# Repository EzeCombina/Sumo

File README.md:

2022: Primera versión del robot ---> ¿?

2023: Segunda versión del robot ---> MEGAPODA - Hecho con SolidWorks 2020 -

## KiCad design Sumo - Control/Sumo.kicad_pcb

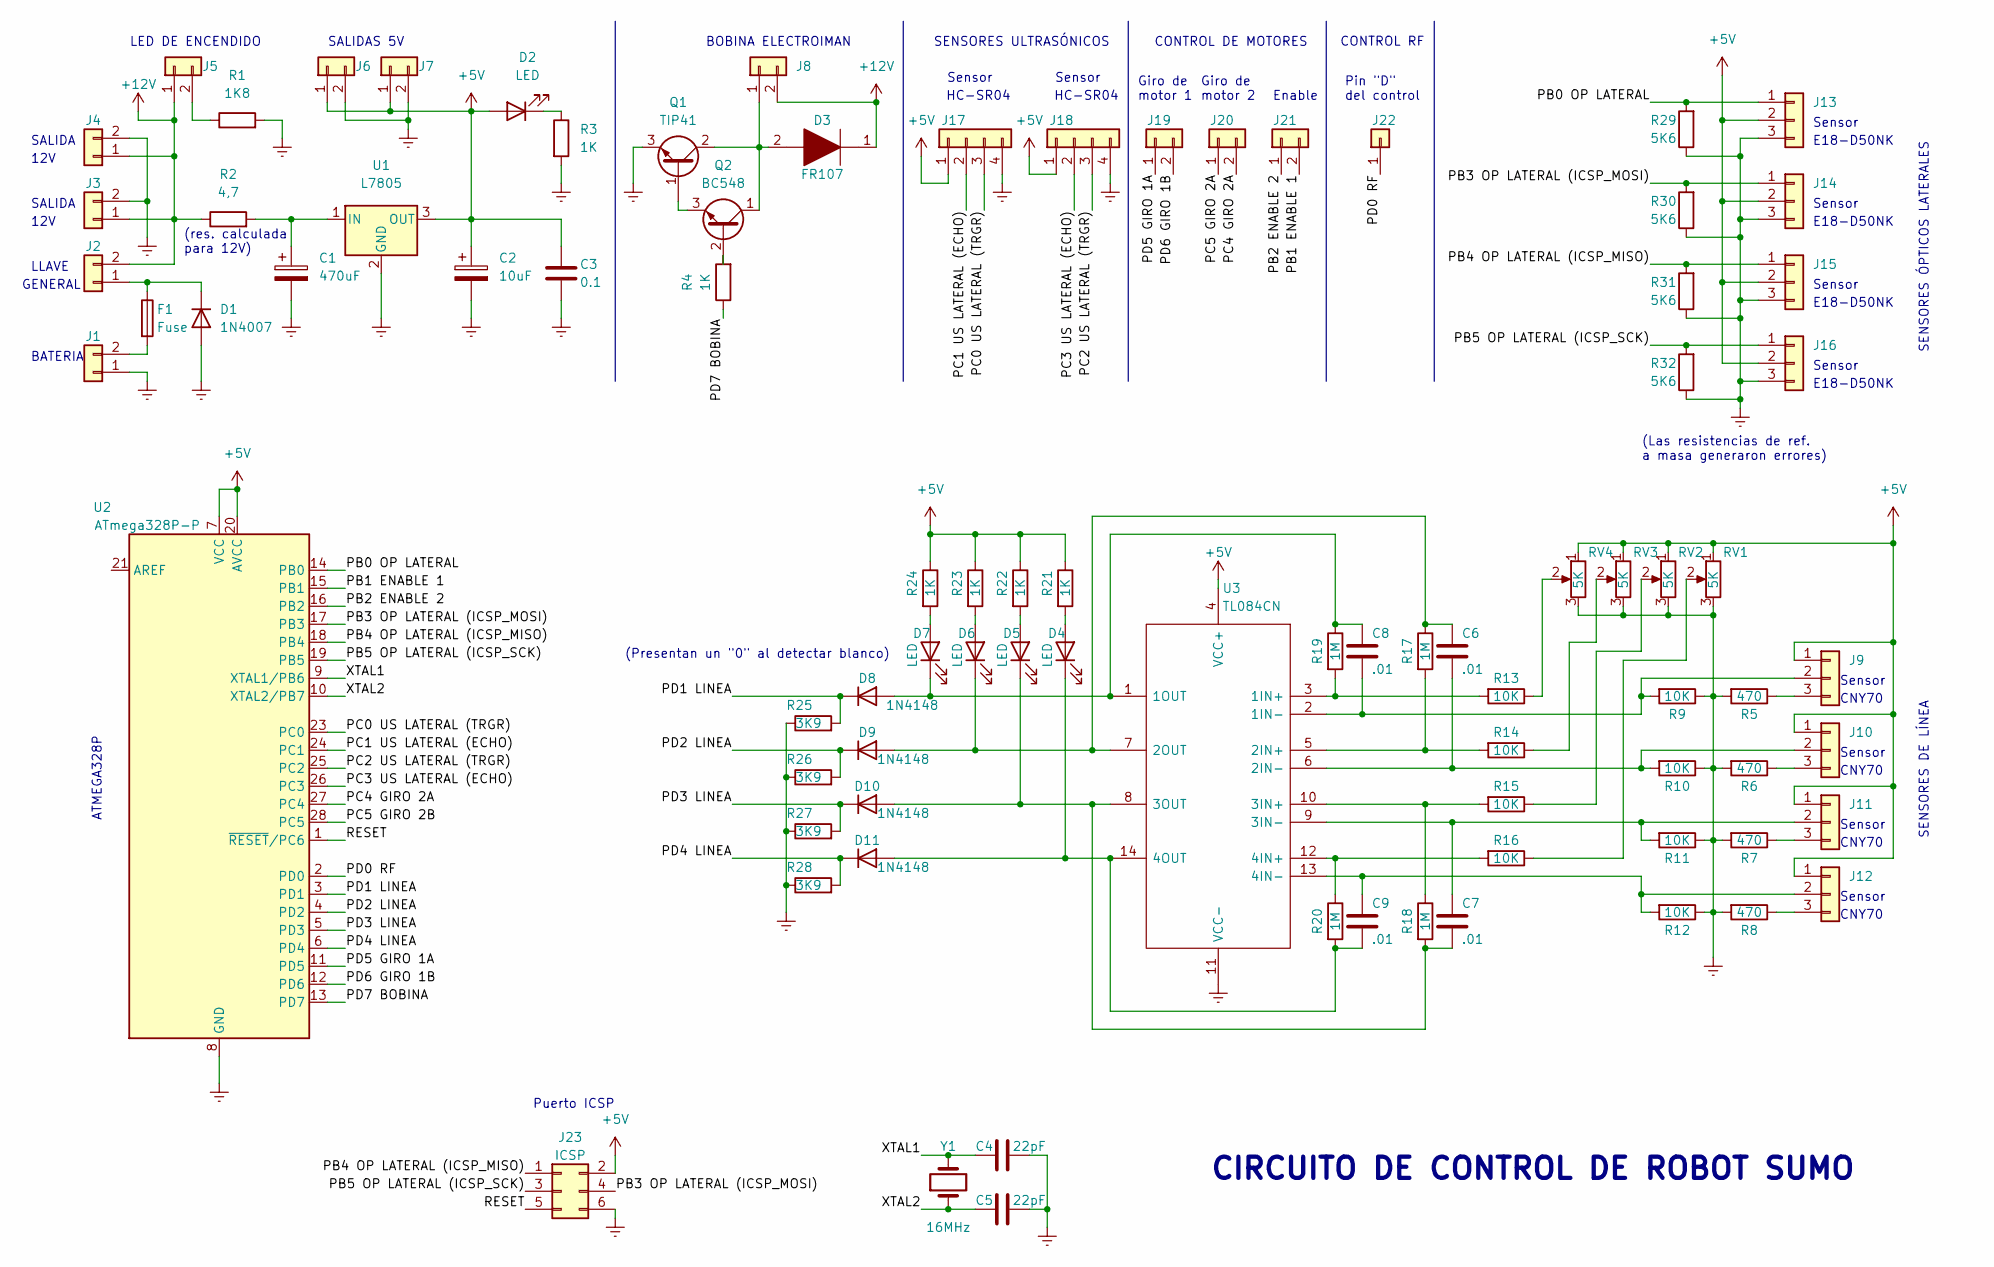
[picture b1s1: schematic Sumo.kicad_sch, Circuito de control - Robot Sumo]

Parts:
C1: 470uF; CP_Radial_D10.0mm_P5.00mm
C2: 10uF; CP_Radial_D5.0mm_P2.00mm
C3: 0.1; C_Disc_D4.3mm_W1.9mm_P5.00mm
C4, C5: 22pF; C_Disc_D4.3mm_W1.9mm_P5.00mm
C6, C7, C8, C9: .01; C_Disc_D4.3mm_W1.9mm_P5.00mm
D1: 1N4007; D_DO-41_SOD81_P10.16mm_Horizontal
D2, D4, D5, D6, D7: LED; LED_D3.0mm
D3: FR107; DIOAD1070W78L470D235P; Manufacturer_Part_Number FR107; Mouser Part Number N/A
D8, D9, D10, D11: 1N4148; D_DO-35_SOD27_P7.62mm_Horizontal
F1: Fuse; JST_PH_B2B-PH-K_1x02_P2.00mm_Vertical
J1, J2, J3, J4, J5, J6, J7, J8, J19, J20: Conn_01x02; JST_PH_B2B-PH-K_1x02_P2.00mm_Vertical
J9: J; JST_PH_B4B-PH-K_1x04_P2.00mm_Vertical
J10, J11, J12, J13, J14, J15, J16: Conn_01x03; JST_PH_B4B-PH-K_1x04_P2.00mm_Vertical
J17, J18: Conn_01x04; JST_PH_B4B-PH-K_1x04_P2.00mm_Vertical
J21: Conn_01x02; JST_EH_B2B-EH-A_1x02_P2.50mm_Vertical
J22: Conn_01x01; JST_EH_B2B-EH-A_1x02_P2.50mm_Vertical
J23: ICSP; PinHeader_2x03_P2.54mm_Vertical
Q1: TIP41; TO-220-3_Vertical
Q2: BC548; TO-92_Inline_Wide
R1: 1K8; R_Axial_DIN0204_L3.6mm_D1.6mm_P7.62mm_Horizontal
R2: 4,7; R_Axial_DIN0204_L3.6mm_D1.6mm_P7.62mm_Horizontal
R3, R4, R21, R22, R23, R24: 1K; R_Axial_DIN0204_L3.6mm_D1.6mm_P7.62mm_Horizontal
R5, R6, R7, R8: 470; R_Axial_DIN0204_L3.6mm_D1.6mm_P5.08mm_Horizontal
R9, R10, R11, R12, R13, R14, R15, R16: 10K; R_Axial_DIN0204_L3.6mm_D1.6mm_P5.08mm_Horizontal
R17, R18, R19, R20: 1M; R_Axial_DIN0204_L3.6mm_D1.6mm_P5.08mm_Horizontal
R25, R26, R27, R28: 3K9; R_Axial_DIN0204_L3.6mm_D1.6mm_P5.08mm_Horizontal
R29, R30, R31, R32: 5K6; R_Axial_DIN0204_L3.6mm_D1.6mm_P5.08mm_Horizontal
RV1, RV2, RV3, RV4: 5K; Potentiometer_Bourns_3296W_Vertical
U1: L7805; TO-220-3_Vertical
U2: ATmega328P-P; DIP-28_W7.62mm
U3: TL084CN; DIP794W53P254L1930H508Q14N; Manufacturer_Part_Number TL084CN; Mouser Part Number 595-TL084CN
Y1: 16MHz; Crystal_HC49-U_Vertical

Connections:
+5V: C2.1, C3.1, D2.2 (A), J6.1, J7.1, J9.1, J10.1, J11.1, J12.1, J13.2, J14.2, J15.2, J16.2, J17.1, J18.1, J23.2, R21.1, R22.1, R23.1, R24.1, RV1.1, RV2.1, RV3.1, RV4.1, U1.3 (OUT), U2.7 (VCC), U2.20 (AVCC), U3.4 (VCC+)
+12V: D3.1, J2.2, J3.1, J4.1, J5.1, J8.2, R2.1
/PB0 OP LATERAL: J13.1, R29.2, U2.14 (PB0)
/PB1 GIRO 2A: J21.2, U2.15 (PB1)
/PB2 GIRO 2B: J21.1, U2.16 (PB2)
/PB3 OP LATERAL (ICSP_MOSI): J14.1, J23.4, R30.2, U2.17 (PB3)
/PB4 OP LATERAL (ICSP_MISO): J15.1, J23.1, R31.2, U2.18 (PB4)
/PB5 OP LATERAL (ICSP_SCK): J16.1, J23.3, R32.2, U2.19 (PB5)
/PC0 US LATERAL (TRGR): J17.3, U2.23 (PC0)
/PC1 US LATERAL (ECHO): J17.2, U2.24 (PC1)
/PC2 US LATERAL (TRGR): J18.3, U2.25 (PC2)
/PC3 US LATERAL (ECHO): J18.2, U2.26 (PC3)
/PD0: J22.1, U2.2 (PD0)
/PD1 LINEA: D8.1 (K), R25.2, U2.3 (PD1)
/PD2 LINEA: D9.1 (K), R26.2, U2.4 (PD2)
/PD3 LINEA: D10.1 (K), R27.2, U2.5 (PD3)
/PD4 LINEA: D11.1 (K), R28.2, U2.6 (PD4)
/PD5 GIRO 1A: J19.1, U2.11 (PD5)
/PD6 GIRO 1B: J19.2, U2.12 (PD6)
/PD7 BOBINA: R4.1, U2.13 (PD7)
/RESET: J23.5, U2.1 (~RESET/PC6)
/XTAL1: C4.2, U2.9 (XTAL1/PB6), Y1.2
/XTAL2: C5.1, U2.10 (XTAL2/PB7), Y1.1
Earth: C1.2, C2.2, C3.2, C4.1, C5.2, D1.2 (A), J1.1, J3.2, J4.2, J6.2, J7.2, J13.3, J13.4, J14.3, J15.3, J16.3, J17.4, J18.4, J23.6, Q1.3 (E), R1.2, R3.2, R5.2, R6.2, R7.2, R8.2, R9.1, R10.1, R11.1, R12.1, R25.1, R26.1, R27.1, R28.1, R29.1, R30.1, R31.1, R32.1, RV1.3, RV2.3, RV3.3, RV4.3, U1.2 (GND), U2.8 (GND), U2.22 (GND), U3.11 (VCC-)
unnamed: C1.1, R2.2, U1.1 (IN)
unnamed: C6.1, J10.2, R10.2, U3.6 (2IN-)
unnamed: C6.2, D6.1 (K), D9.2 (A), R17.1, U3.7 (2OUT)
unnamed: C7.1, D5.1 (K), D10.2 (A), R18.2, U3.8 (3OUT)
unnamed: C7.2, J11.2, R11.2, U3.9 (3IN-)
unnamed: C8.1, J9.2, R9.2, U3.2 (1IN-)
unnamed: C8.2, D7.1 (K), D8.2 (A), R19.1, U3.1 (1OUT)
unnamed: C9.1, D4.1 (K), D11.2 (A), R20.2, U3.14 (4OUT)
unnamed: C9.2, J12.2, R12.2, U3.13 (4IN-)
unnamed: D1.1 (K), F1.1, J2.1
unnamed: D2.1 (K), R3.1
unnamed: D3.2, J8.1, Q1.2 (C), Q2.1 (C)
unnamed: D4.2 (A), R21.2
unnamed: D5.2 (A), R22.2
unnamed: D6.2 (A), R23.2
unnamed: D7.2 (A), R24.2
unnamed: F1.2, J1.2
unnamed: J5.2, R1.1
unnamed: J9.3, R5.1
unnamed: J10.3, R6.1
unnamed: J11.3, R7.1
unnamed: J12.3, R8.1
unnamed: Q1.1 (B), Q2.3 (E)
unnamed: Q2.2 (B), R4.2
unnamed: R13.1, RV4.2
unnamed: R13.2, R19.2, U3.3 (1IN+)
unnamed: R14.1, RV3.2
unnamed: R14.2, R17.2, U3.5 (2IN+)
unnamed: R15.1, RV2.2
unnamed: R15.2, R18.1, U3.10 (3IN+)
unnamed: R16.1, RV1.2
unnamed: R16.2, R20.1, U3.12 (4IN+)

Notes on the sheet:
SENSORES DE LÍNEA
SENSORES ÓPTICOS LATERALES
E18-D50NK
LED DE ENCENDIDO
Puerto ICSP
(Presentan un "0" al detectar blanco)
CNY70
12V
Sensor
SENSORES ULTRASÓNICOS
Enable
Giro de motor 1
Pin "D" del control
Giro de motor 2
SALIDA
GENERAL
BOBINA ELECTROIMAN
LLAVE
BATERIA
CONTROL RF
(res. calculada para 12V)
ATMEGA328P
CONTROL DE MOTORES
CIRCUITO DE CONTROL DE ROBOT SUMO
HC-SR04
(Las resistencias de ref. a masa generaron errores)
SALIDAS 5V

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
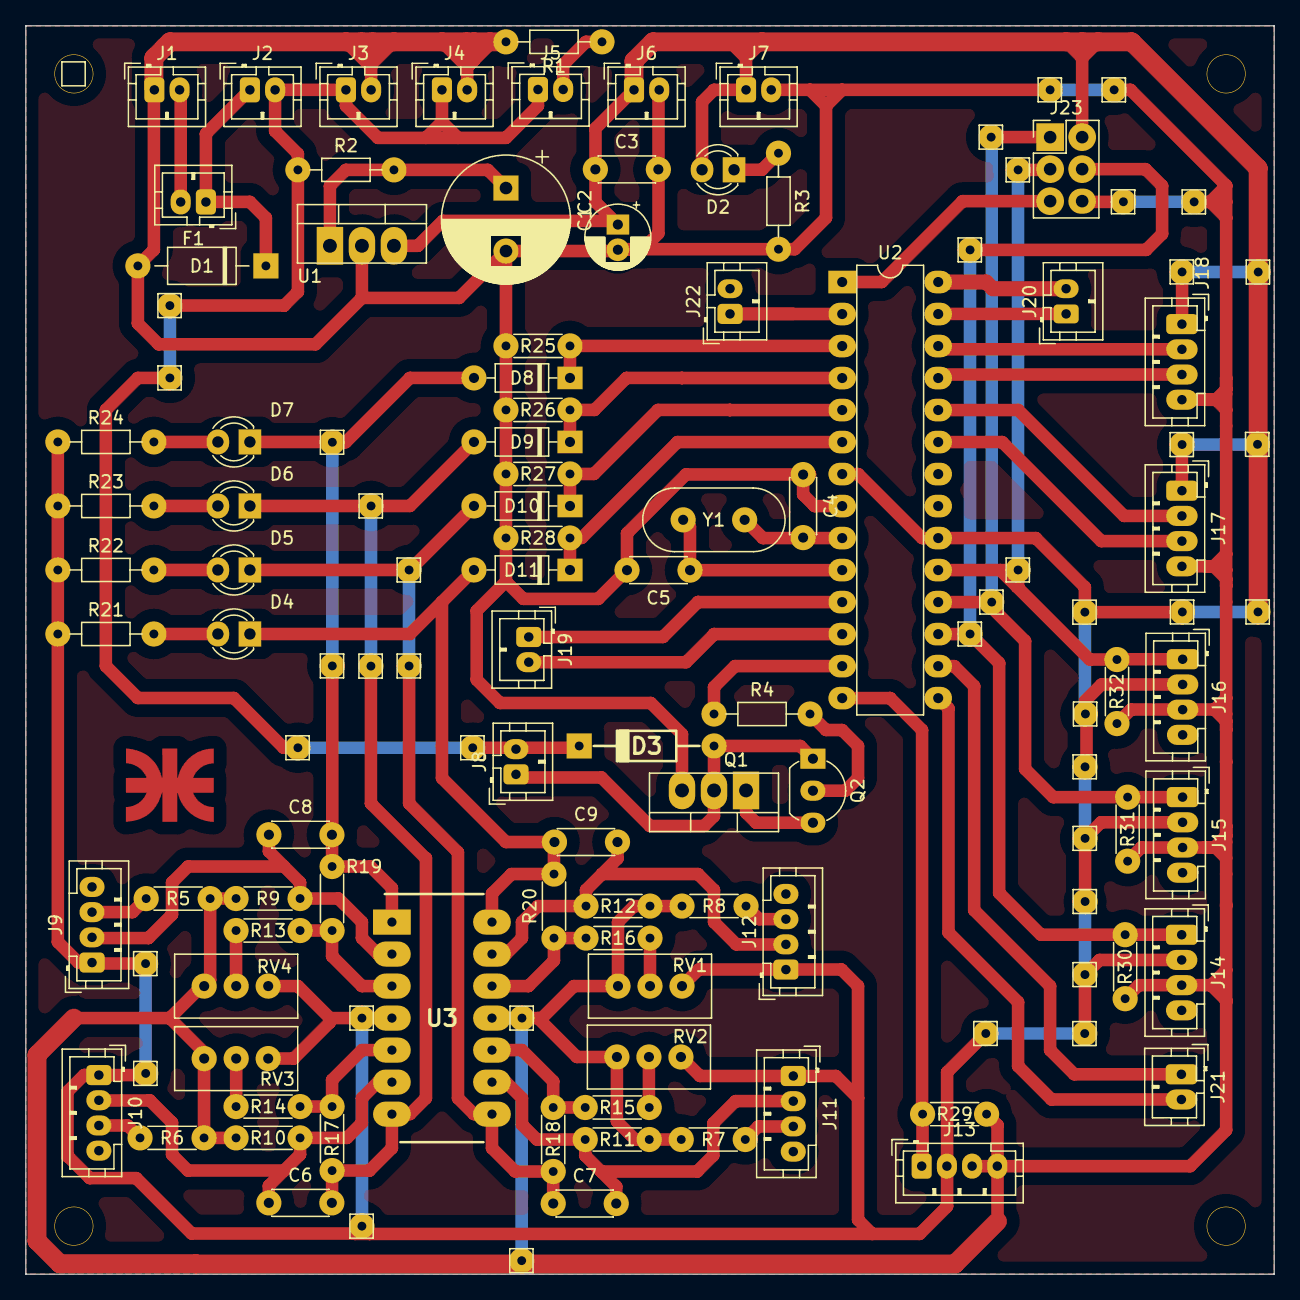
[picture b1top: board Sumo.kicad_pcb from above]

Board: 2 copper layers, 99.1 x 99.1 mm, 86 parts (0 on the bottom side), 58 nets.

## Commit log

2023-11-08 Second Commit
2024-07-31 Robot sumo 2023
